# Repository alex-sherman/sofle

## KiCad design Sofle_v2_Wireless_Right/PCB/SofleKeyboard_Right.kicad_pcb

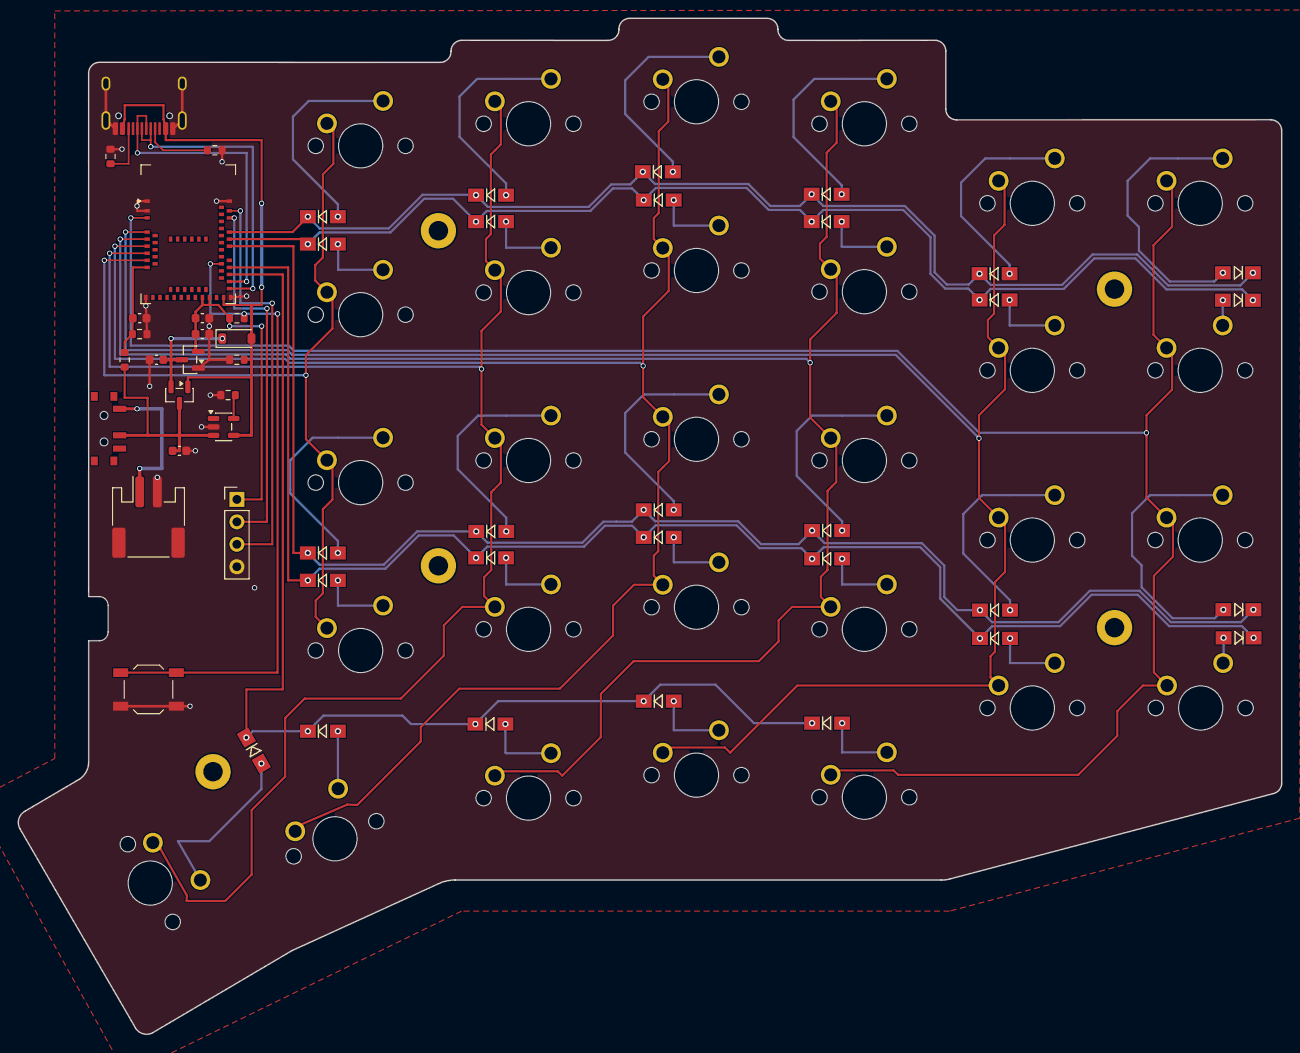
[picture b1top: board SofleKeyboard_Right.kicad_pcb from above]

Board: 2 copper layers, 142.9 x 114.9 mm, 85 parts (0 on the bottom side), 55 nets.

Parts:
C1, C2, C3: 10uF; C_0603_1608Metric
C4, C5: 100nF; C_0603_1608Metric
D1, D2, D3, D4, D5, D6, D7, D8, D9, D10, D11, D12, D13, D14, D15, D16, D17, D18, D19, D20, D21, D22, D23, D24, D26, D27, D28, D29, D30: D; Diode_SOD123
D_PWR: 1N5819WS; D_SOD-123
J1: USB_C_Receptacle_USB2.0_16P; USB_C_Receptacle_HRO_TYPE-C-31-M-12
J_BAT: Conn_01x02; JST_PH_S2B-PH-SM4-TB_1x02-1MP_P2.00mm_Horizontal
J_SWD: Conn_01x04; PinHeader_1x04_P2.54mm_Vertical
Q1: AO3401A; SOT-23
R1, R2: 5.1k; R_0603_1608Metric
R3: 2.0k; R_0603_1608Metric
R4: 10k; R_0603_1608Metric
R5, R7: 100k; R_0603_1608Metric
R6: 220k; R_0603_1608Metric
SW1, SW2, SW3, SW4, SW5, SW6, SW7, SW8, SW9, SW10, SW11, SW12, SW13, SW14, SW15, SW16, SW17, SW18, SW19, SW20, SW21, SW22, SW23, SW24, SW27, SW28, SW29, SW30: SW_PUSH; MXOnly-1U-NoLED
SW26: SW_PUSH; MXOnly-1.5U-NoLED
SW_PWR: SW_SPDT; SW_SPDT_PCM12
SW_RST: SW_Push; SW_SPST_TL3342
TH3, TH4, TH5, TH6, TH7: HOLE; HOLE_M2_TH
U1: MDBT50Q-1MV2; Raytac_MDBT50Q
U2: TP4054; SOT-23-5
U3: XC6206P332MR; SOT-23

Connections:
3V3: C3.1, C4.1, J_SWD.1, R4.2, U1.28, U1.30, U3.2
CC1: J1.A5, R1.1
CC2: J1.B5, R2.1
GND: C1.2, C2.2, C3.2, C4.2, C5.2, J1.A1, J1.A12, J1.B1, J1.B12, J1.SH, J_BAT.2, J_BAT.MP, J_SWD.4, R1.2, R2.2, R3.2, R6.2, R7.2, SW_RST.2, U1.1, U1.2, U1.15, U1.33, U1.55, U2.2, U3.1
unnamed: D1.2 (A), SW1.2
unnamed: D2.2 (A), SW2.2
unnamed: D3.2 (A), SW3.2
unnamed: D4.2 (A), SW4.2
unnamed: D5.2 (A), SW5.2
unnamed: D6.2 (A), SW6.2
unnamed: D7.2 (A), SW7.2
unnamed: D8.2 (A), SW8.2
unnamed: D9.2 (A), SW9.2
unnamed: D10.2 (A), SW10.2
unnamed: D11.2 (A), SW11.2
unnamed: D12.2 (A), SW12.2
unnamed: D13.2 (A), SW13.2
unnamed: D14.2 (A), SW14.2
unnamed: D15.2 (A), SW15.2
unnamed: D16.2 (A), SW16.2
unnamed: D17.2 (A), SW17.2
unnamed: D18.2 (A), SW18.2
unnamed: D19.2 (A), SW19.2
unnamed: D20.2 (A), SW20.2
unnamed: D21.2 (A), SW21.2
unnamed: D22.2 (A), SW22.2
unnamed: D23.2 (A), SW23.2
unnamed: D24.2 (A), SW24.2
unnamed: D26.2 (A), SW26.2
unnamed: D27.2 (A), SW27.2
unnamed: D28.2 (A), SW28.2
unnamed: D29.2 (A), SW29.2
unnamed: D30.2 (A), SW30.2
PROG: R3.1, U2.5
RESET: R4.1, SW_RST.1, U1.40
SW25A: SW1.1, SW7.1, SW13.1, SW19.1, U1.12
SWDCLK: J_SWD.3, U1.53
SWDIO: J_SWD.2, U1.51
USB_D_N: J1.A7, J1.B7, U1.34
USB_D_P: J1.A6, J1.B6, U1.35
VBAT_RAW: J_BAT.1, SW_PWR.1
VBAT_SENSE: C5.1, R5.1, R6.1, U1.14
VBAT_SW: C1.1, Q1.3, R5.2, SW_PWR.2, U2.3
VBUS: D_PWR.2, J1.A4, J1.A9, J1.B4, J1.B9, Q1.1, R7.1, U1.32, U2.4
V_SYS: C2.1, D_PWR.1, Q1.2, U3.3
col0: SW6.1, SW12.1, SW18.1, SW24.1, SW30.1, U1.3
col1: SW5.1, SW11.1, SW17.1, SW23.1, SW29.1, U1.4
col2: SW4.1, SW10.1, SW16.1, SW22.1, SW28.1, U1.6
col3: SW3.1, SW9.1, SW15.1, SW21.1, SW27.1, U1.8
col4: SW2.1, SW8.1, SW14.1, SW20.1, SW26.1, U1.10
row0: D1.1 (K), D2.1 (K), D3.1 (K), D4.1 (K), D5.1 (K), D6.1 (K), U1.48
row1: D7.1 (K), D8.1 (K), D9.1 (K), D10.1 (K), D11.1 (K), D12.1 (K), U1.46
row2: D13.1 (K), D14.1 (K), D15.1 (K), D16.1 (K), D17.1 (K), D18.1 (K), U1.44
row3: D19.1 (K), D20.1 (K), D21.1 (K), D22.1 (K), D23.1 (K), D24.1 (K), U1.39
row4: D26.1 (K), D27.1 (K), D28.1 (K), D29.1 (K), D30.1 (K), U1.37

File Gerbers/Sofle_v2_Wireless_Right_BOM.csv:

Comment,Designator,Footprint,LCSC Part #
"1N4148W","D1,D2,D3,D4,D5,D6,D7,D8,D9,D10,D11,D12,D13,D14,D15,D16,D17,D18,D19,D20,D21,D22,D23,D24,D26,D27,D28,D29,D30","SOD-123","C81598"
"MDBT50Q-1MV2","U1","Raytac_MDBT50Q","C5118826"
"TYPE-C-31-M-12","J1","USB_C_Receptacle_HRO_TYPE-C-31-M-12","C165948"
"TP4054","U2","SOT-23-5","C32574"
"XC6206P332MR","U3","SOT-23","C5446"
"AO3401A","Q1","SOT-23","C15127"
"1N5819WS","D_PWR","SOD-123","C8598"
"PCM12SMTR","SW_PWR","SW_SPDT_PCM12","C431540"
"S2B-PH-SM4-TB","J_BAT","JST_PH_S2B-PH-SM4-TB_1x02-1MP_P2.00mm_Horizontal","C295747"
"TL3342","SW_RST","SW_SPST_TL3342","C318884"
"5.1k","R1,R2","0603","C23186"
"2.0k","R3","0603","C4190"
"10k","R4","0603","C25804"
"100k","R5,R7","0603","C25803"
"220k","R6","0603","C25905"
"10uF","C1,C2,C3","0603","C19702"
"100nF","C4,C5","0603","C14663"

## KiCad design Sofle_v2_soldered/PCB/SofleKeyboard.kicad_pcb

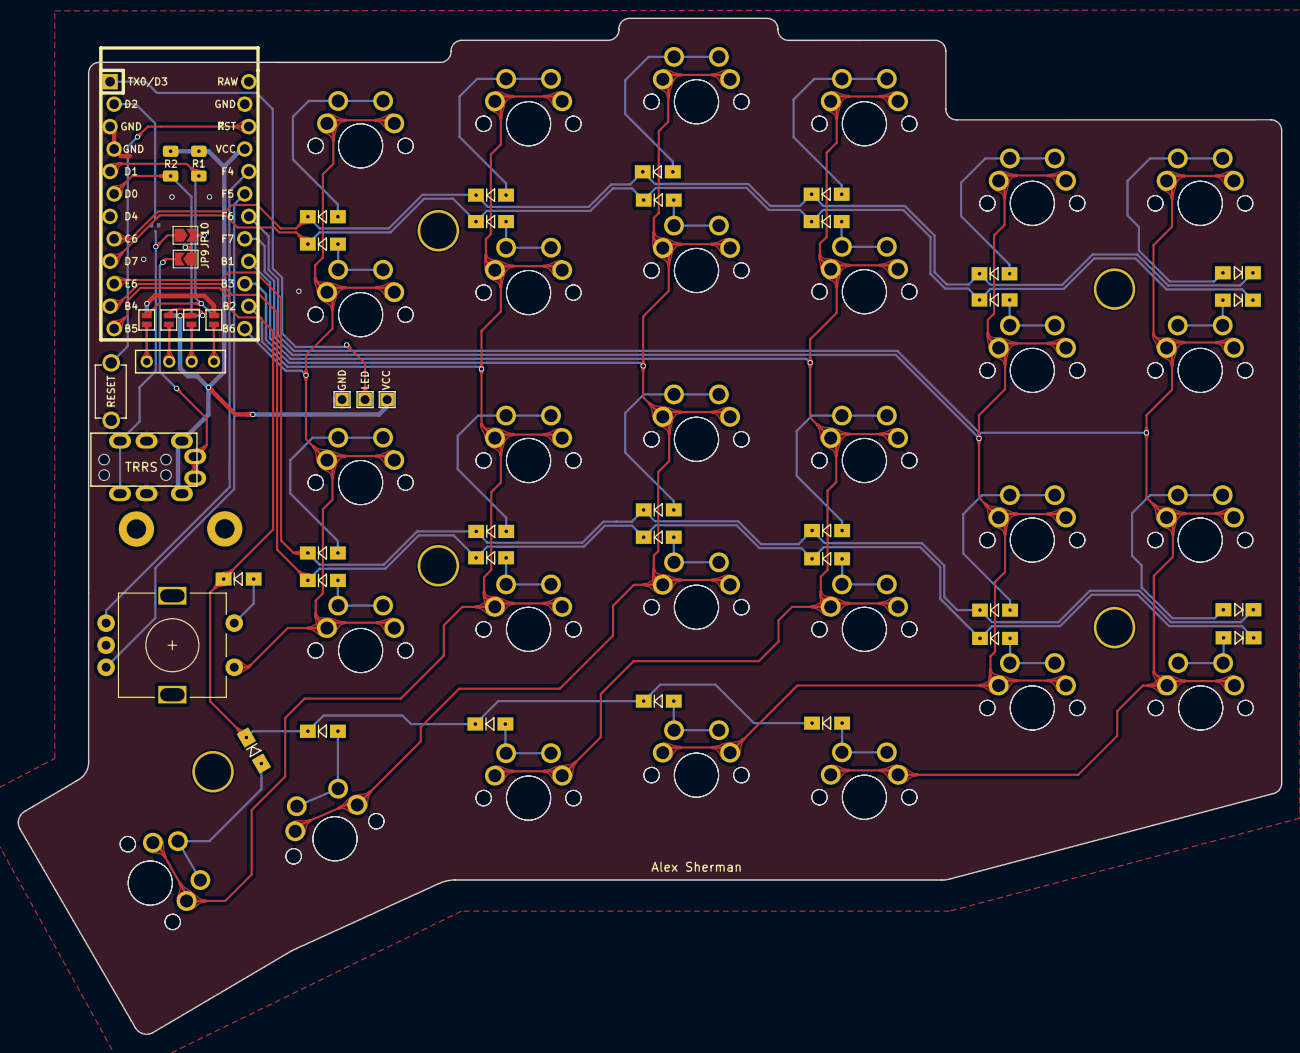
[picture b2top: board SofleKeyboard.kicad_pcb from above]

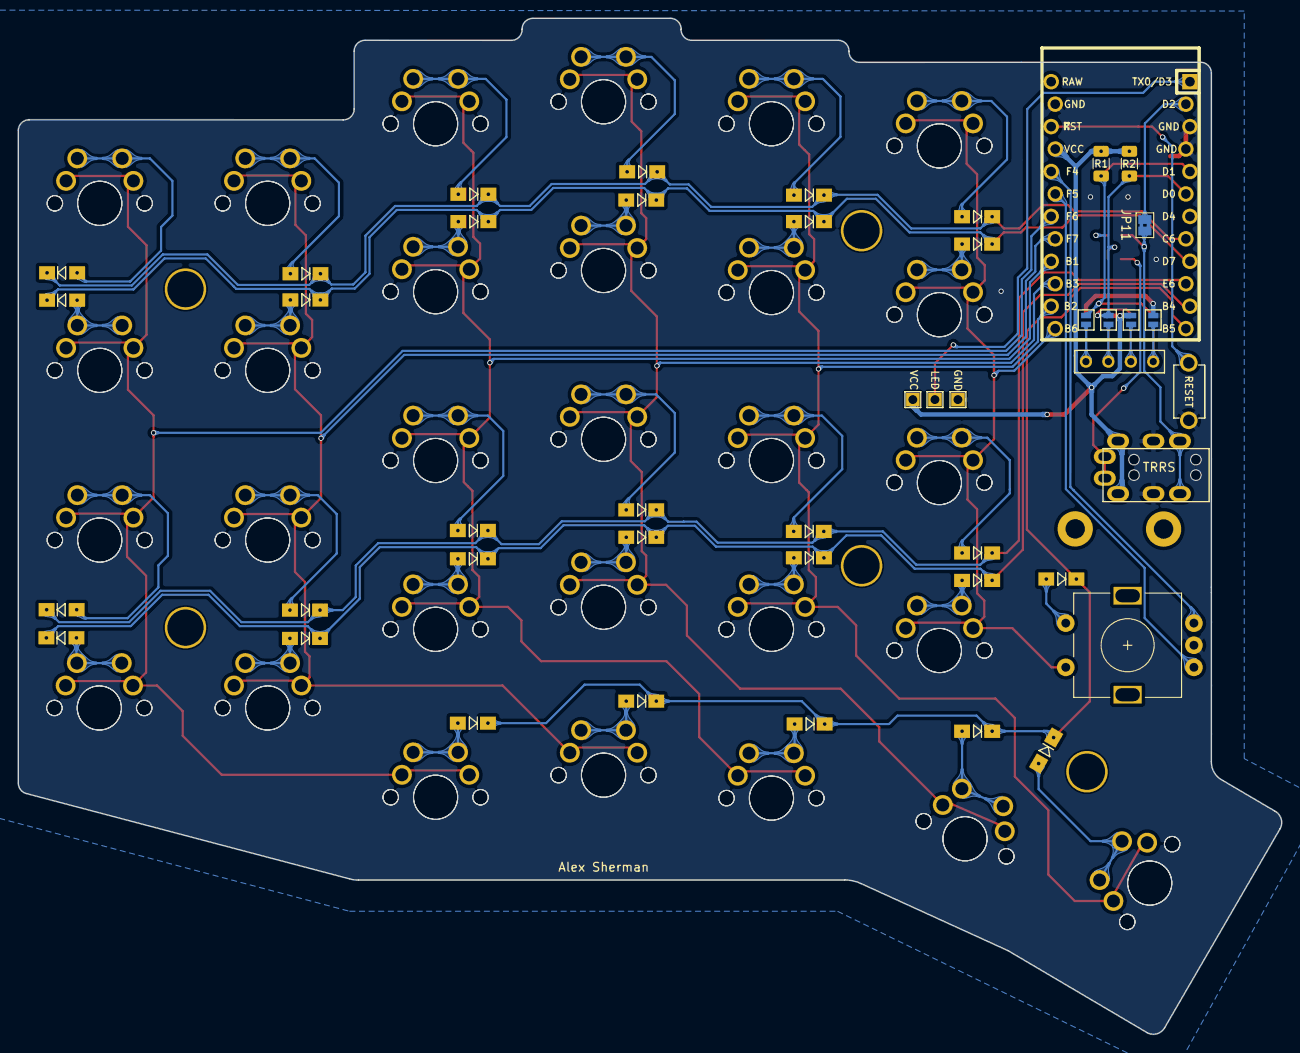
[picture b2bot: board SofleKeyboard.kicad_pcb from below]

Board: 2 copper layers, 142.9 x 114.9 mm, 114 parts (36 on the bottom side), 56 nets.

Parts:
D1, D2, D3, D4, D5, D6, D7, D8, D9, D10, D11, D12, D13, D14, D15, D16, D17, D18, D19, D20, D21, D22, D23, D24, D25, D26, D27, D28, D29, D30: D; Diode_SOD123
J1: LED
J2: 4PIN; MJ-4PP-9
J3: OLED; OLED_4Pin
JP1, JP2, JP3, JP4, JP5, JP6, JP7, JP8: Jumper_NO_Small; Jumper
JP9: I2CSCL; SolderJumper-2_P1.3mm_Open_TrianglePad1.0x1.5mm
JP10: IC2SDA; SolderJumper-2_P1.3mm_Open_TrianglePad1.0x1.5mm
JP11: Serial; SolderJumper-2_P1.3mm_Bridged2Bar_Pad1.0x1.5mm
R1, R2: R; R_1206_DoubleSided
RSW1: SW_RST; TACT_SWITCH_TVBP06
SW1, SW1#2, SW2, SW2#2, SW3, SW3#2, SW4, SW4#2, SW5, SW5#2, SW6, SW6#2, SW7, SW7#2, SW8, SW8#2, SW9, SW9#2, SW10, SW10#2, SW11, SW11#2, SW12, SW12#2, SW13, SW13#2, SW14, SW14#2, SW15, SW15#2, SW16, SW16#2, SW17, SW17#2, SW18, SW18#2, SW19, SW19#2, SW20, SW20#2, SW21, SW21#2, SW22, SW22#2, SW23, SW23#2, SW24, SW24#2, SW27, SW27#2, SW28, SW28#2, SW29, SW29#2, SW30, SW30#2: SW_PUSH; MXOnly-1U-NoLED
SW25: Rotary_Encoder_Switch; RotaryEncoder_Alps_EC11E-Switch_Vertical_H20mm-keebio_modif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
SW26, SW26#2: SW_PUSH; MXOnly-1.5U-NoLED
TH1, TH2: HOLE; M2_HOLE_PCB
TH3, TH4, TH5, TH6, TH7: HOLE; HOLE_M2_TH
U1: ProMicro; ArduinoProMicro-ZigZag-DoubleSided

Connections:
/i2c_c: J2.4, JP9.2
/i2c_d: J2.3, JP10.1, JP11.2
DATA: JP11.1, U1.2 (RX(PD2))
ENCA: SW25.A, U1.20 (A3(PF4))
ENCB: SW25.B, U1.19 (A2(PF5))
GND: J1.3, J2.2, JP1.2, JP8.2, RSW1.1, SW25.C, U1.3 (GND), U1.4 (GND), U1.23 (GND)
LED: J1.2, U1.1 (TX(PD3))
unnamed: D1.2 (A), SW1.2, SW1#2.2
unnamed: D2.2 (A), SW2.2, SW2#2.2
unnamed: D3.2 (A), SW3.2, SW3#2.2
unnamed: D4.2 (A), SW4.2, SW4#2.2
unnamed: D5.2 (A), SW5.2, SW5#2.2
unnamed: D6.2 (A), SW6.2, SW6#2.2
unnamed: D7.2 (A), SW7.2, SW7#2.2
unnamed: D8.2 (A), SW8.2, SW8#2.2
unnamed: D9.2 (A), SW9.2, SW9#2.2
unnamed: D10.2 (A), SW10.2, SW10#2.2
unnamed: D11.2 (A), SW11.2, SW11#2.2
unnamed: D12.2 (A), SW12.2, SW12#2.2
unnamed: D13.2 (A), SW13.2, SW13#2.2
unnamed: D14.2 (A), SW14.2, SW14#2.2
unnamed: D15.2 (A), SW15.2, SW15#2.2
unnamed: D16.2 (A), SW16.2, SW16#2.2
unnamed: D17.2 (A), SW17.2, SW17#2.2
unnamed: D18.2 (A), SW18.2, SW18#2.2
unnamed: D19.2 (A), SW19.2, SW19#2.2
unnamed: D20.2 (A), SW20.2, SW20#2.2
unnamed: D21.2 (A), SW21.2, SW21#2.2
unnamed: D22.2 (A), SW22.2, SW22#2.2
unnamed: D23.2 (A), SW23.2, SW23#2.2
unnamed: D24.2 (A), SW24.2, SW24#2.2
unnamed: D26.2 (A), SW26.2, SW26#2.2
unnamed: D27.2 (A), SW27.2, SW27#2.2
unnamed: D28.2 (A), SW28.2, SW28#2.2
unnamed: D29.2 (A), SW29.2, SW29#2.2
unnamed: D30.2 (A), SW30.2, SW30#2.2
unnamed: J3.1, JP4.1, JP8.1
unnamed: J3.2, JP3.1, JP7.1
unnamed: J3.3, JP2.1, JP6.1
unnamed: J3.4, JP1.1, JP5.1
RESET: RSW1.2, U1.22 (RST)
SCL: JP3.2, JP6.2, JP9.1, R2.2, U1.6 (SCL(PD0))
SDA: JP4.2, JP5.2, JP10.2, R1.2, U1.5 (SDA(PD1))
SW25A: SW1.1, SW1#2.1, SW7.1, SW7#2.1, SW13.1, SW13#2.1, SW19.1, SW19#2.1, SW25.S1, U1.13 (D10(PB6))
SW25B: D25.2 (A), SW25.S2
VCC: J1.1, J2.1, JP2.2, JP7.2, R1.1, R2.1, U1.21 (VCC)
col0: SW6.1, SW6#2.1, SW12.1, SW12#2.1, SW18.1, SW18#2.1, SW24.1, SW24#2.1, SW30.1, SW30#2.1, U1.18 (A1(PF6))
col1: SW5.1, SW5#2.1, SW11.1, SW11#2.1, SW17.1, SW17#2.1, SW23.1, SW23#2.1, SW29.1, SW29#2.1, U1.17 (A0(PF7))
col2: SW4.1, SW4#2.1, SW10.1, SW10#2.1, SW16.1, SW16#2.1, SW22.1, SW22#2.1, SW28.1, SW28#2.1, U1.16 (D15(PB1))
col3: SW3.1, SW3#2.1, SW9.1, SW9#2.1, SW15.1, SW15#2.1, SW21.1, SW21#2.1, SW27.1, SW27#2.1, U1.15 (D14(PB3))
col4: SW2.1, SW2#2.1, SW8.1, SW8#2.1, SW14.1, SW14#2.1, SW20.1, SW20#2.1, SW26.1, SW26#2.1, U1.14 (D16(PB2))
row0: D1.1 (K), D2.1 (K), D3.1 (K), D4.1 (K), D5.1 (K), D6.1 (K), U1.8 (D5(PC6))
row1: D7.1 (K), D8.1 (K), D9.1 (K), D10.1 (K), D11.1 (K), D12.1 (K), U1.9 (D6(PD7))
row2: D13.1 (K), D14.1 (K), D15.1 (K), D16.1 (K), D17.1 (K), D18.1 (K), U1.10 (D7(PE6))
row3: D19.1 (K), D20.1 (K), D21.1 (K), D22.1 (K), D23.1 (K), D24.1 (K), U1.11 (D8(PB4))
row4: D25.1 (K), D26.1 (K), D27.1 (K), D28.1 (K), D29.1 (K), D30.1 (K), U1.12 (D9(PB5))

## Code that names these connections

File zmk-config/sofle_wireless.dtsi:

/*
 * ZMK Common Devicetree Definition for Sofle v2 Wireless (Left & Right PCBs)
 * MCU Module: Raytac MDBT50Q-1MV2 (nRF52840)
 *
 * Matrix Pinout (shared on both Left and Right PCBs):
 *   row0: P0.24 (MDBT50Q Pin 48)
 *   row1: P0.22 (MDBT50Q Pin 46)
 *   row2: P0.20 (MDBT50Q Pin 44)
 *   row3: P0.15 (MDBT50Q Pin 39)
 *   row4: P0.13 (MDBT50Q Pin 37)
 *
 *   col0 (SW6/12/18/24/30): P1.10 (MDBT50Q Pin 3)
 *   col1 (SW5/11/17/23/29): P1.11 (MDBT50Q Pin 4)
 *   col2 (SW4/10/16/22/28): P1.13 (MDBT50Q Pin 6)
 *   col3 (SW3/9/15/21/27):  P1.15 (MDBT50Q Pin 8)
 *   col4 (SW2/8/14/20/26):  P0.29 (MDBT50Q Pin 10)
 *   col5 (SW1/7/13/19):     P0.31 (MDBT50Q Pin 12)
 *
 * Battery Voltage Divider:
 *   VBAT_SENSE: P0.30 / AIN6 (MDBT50Q Pin 14), R5 = 100k (high side), R6 = 220k (low side)
 */

#include <dt-bindings/zmk/matrix_transform.h>

/ {
    chosen {
        zmk,kscan = &kscan0;
        zmk,matrix-transform = &default_transform;
        zmk,battery = &vbatt;
    };

    default_transform: keymap_transform_0 {
        compatible = "zmk,matrix-transform";
        columns = <12>;
        rows = <5>;
        /*
         * 58-key Sofle v2 layout (Rotary encoders SW25 removed on both halves):
         * Row 0: 6 left + 6 right
         * Row 1: 6 left + 6 right
         * Row 2: 6 left + 6 right
         * Row 3: 6 left + 6 right
         * Row 4: 5 left thumb + 5 right thumb
         */
        map = <
            RC(0,0) RC(0,1) RC(0,2) RC(0,3) RC(0,4) RC(0,5)                 RC(0,6) RC(0,7) RC(0,8) RC(0,9) RC(0,10) RC(0,11)
            RC(1,0) RC(1,1) RC(1,2) RC(1,3) RC(1,4) RC(1,5)                 RC(1,6) RC(1,7) RC(1,8) RC(1,9) RC(1,10) RC(1,11)
            RC(2,0) RC(2,1) RC(2,2) RC(2,3) RC(2,4) RC(2,5)                 RC(2,6) RC(2,7) RC(2,8) RC(2,9) RC(2,10) RC(2,11)
            RC(3,0) RC(3,1) RC(3,2) RC(3,3) RC(3,4) RC(3,5)                 RC(3,6) RC(3,7) RC(3,8) RC(3,9) RC(3,10) RC(3,11)
                    RC(4,0) RC(4,1) RC(4,2) RC(4,3) RC(4,4)                 RC(4,7) RC(4,8) RC(4,9) RC(4,10) RC(4,11)
        >;
    };

    kscan0: kscan {
        compatible = "zmk,kscan-gpio-matrix";
        wakeup-source;
        diode-direction = "col2row";

        row-gpios
            = <&gpio0 24 (GPIO_ACTIVE_HIGH | GPIO_PULL_DOWN)>
            , <&gpio0 22 (GPIO_ACTIVE_HIGH | GPIO_PULL_DOWN)>
            , <&gpio0 20 (GPIO_ACTIVE_HIGH | GPIO_PULL_DOWN)>
            , <&gpio0 15 (GPIO_ACTIVE_HIGH | GPIO_PULL_DOWN)>
            , <&gpio0 13 (GPIO_ACTIVE_HIGH | GPIO_PULL_DOWN)>
            ;
    };

    vbatt: vbatt {
        compatible = "zmk,battery-voltage-divider";
        io-channels = <&adc 6>; /* P0.30 = AIN6 */
        output-ohms = <220000>; /* R6 = 220k */
        full-ohms = <(100000 + 220000)>; /* R5 = 100k + R6 = 220k */
    };
};

&adc {
    status = "okay";
};

&gpiote {
    status = "okay";
};

&gpio0 {
    status = "okay";
};

&gpio1 {
    status = "okay";
};

&usbd {
    status = "okay";
};
